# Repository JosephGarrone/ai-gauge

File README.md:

# AI-Gauge

Customisable automotive dial gauge firmware for the Waveshare
**ESP32-S3-Touch-AMOLED-1.75** (466×466 round AMOLED).

Replaces physical boost and EGT gauges, re-using the vehicle's existing sensors through an
external signal-conditioning front-end. The gauge face is defined in XML, so it can be
restyled without rebuilding firmware.

## Goals

- **60fps+**, always. A laggy needle is worse than the analogue gauge it replaces.
- **XML-defined faces** — restyle over WiFi, no rebuild, including your own tick, needle and hub
  shapes, designed in the browser with the face editor.
- **Portable** to square and other round panels via a board profile.
- **Swipe up** from the dial for settings.
- **WiFi** for config upload, OTA, and telemetry feeds pushed from other devices.

## Getting started

```bash
. ~/esp/v5.5.1/esp-idf/export.sh
idf.py -C firmware set-target esp32s3
idf.py -C firmware -p <PORT> flash monitor
```

Full instructions: [docs/build-and-flash.md](docs/build-and-flash.md).

Not developing the firmware? Every tagged release publishes a browser-based installer — flash
from Chrome or Edge with no toolchain. See [docs/ci-release.md](docs/ci-release.md).

To design a face, open the **face editor**: watch it move, check exactly what the gauge will make of
it, and download the XML. Every gauge serves it at `http://ai-gauge-XXXX.local/editor/`, and opened
from there it uploads straight to that gauge. A copy for designing without a gauge is at `/editor/`
on the GitHub Pages site. See [docs/config-app.md](docs/config-app.md).

## Documentation

Start with **[AGENTS.md](AGENTS.md)** for the design decisions and the conventions this
project follows, then [docs/](docs/) for detail:

| Document | Contents |
|---|---|
| [architecture.md](docs/architecture.md) | Components, task model, data flow |
| [display-pipeline.md](docs/display-pipeline.md) | Frame budget and how 60fps is achieved |
| [gauge-config-schema.md](docs/gauge-config-schema.md) | The gauge XML format |
| [gauge-xml-interface.md](docs/gauge-xml-interface.md) | Authoring guide for tools that write gauge XML |
| [config-app.md](docs/config-app.md) | The face editor web app |
| [hardware-reference.md](docs/hardware-reference.md) | GPIO map, I2C addresses, warnings |
| [sensor-frontend.md](docs/sensor-frontend.md) | Boost and EGT signal conditioning |
| [rear-pcb.md](docs/rear-pcb.md) | Planned rear PCB: power, daisy chain, sensors |
| [rear-pcb-parts.md](docs/rear-pcb-parts.md) | Rear PCB parts list, pinouts and wiring diagrams |
| [networking.md](docs/networking.md) | Provisioning, HTTP API, telemetry, OTA |
| [performance.md](docs/performance.md) | Measurement method and results |
| [roadmap.md](docs/roadmap.md) | Milestones and what is planned next |
| [adr/](docs/adr/) | Why things are the way they are |

## Status

Running on hardware. The sensor board has been designed and sent for fabrication, and the
firmware to read it is written, but it has not met a board yet. Until one answers, the needle
shows a **simulated** sweep.

**Working today:** the dial renders from an XML configuration held on flash, with colour
bands, ticks, labels and a damped needle. Crossing an alert threshold flashes the needle in the
alert colour. A peak-hold marker records the highest reading on the dial; tap the dial to reset
it. Long-press the dial to recall the session minimum and maximum for 3s; long-press again
while they show to reset them. Swipe up for settings — pick a different gauge, adjust brightness, rotate the screen in 90°
steps to suit how the gauge is mounted, cap the frame rate at 30, 45 or 60 fps or leave it
uncapped, toggle an FPS badge, and read live
frame statistics and firmware information. Choices persist across
reboots. The settings page also shows live sensor readings and faults, has a **Zero boost now**
button, and holds the sensor calibration (sensor range and output voltages, divider trims, EGT
offset, smoothing, auto-zero).

There is no audible alert: no speaker will be fitted, so the chime was removed.

Over WiFi, the gauge is set up from a phone and then reachable at `ai-gauge-XXXX.local`. Its HTTP
API uploads new gauge faces and applies them live, accepts telemetry from other devices, and
installs firmware updates, rolling back automatically if an update fails to start. See
[docs/networking.md](docs/networking.md); note the API is unauthenticated, so use it only on a
network you trust.

A missing or malformed configuration falls back to the next available one, and then to a
compiled-in face, always saying on the settings page what went wrong. A bad config file must
never leave a driver looking at a blank screen.

**Measured on hardware** (ESP32-S3 rev v0.2), needle sweeping continuously with WiFi connected,
peak-hold and audio running:

| | Result |
|---|---|
| Frame rate | **66.7 fps** (the LVGL refresh ceiling, not a rendering limit) |
| Screen redrawn per frame | ~13% |
| Render time | ~7.7 ms of each 15 ms period |
| Swipe transition | ~33 fps — a documented, accepted trade |
| Internal RAM free after startup | ~8.6 KB — the board's scarcest resource |

CPU is not the constraint on this board; **internal RAM is**. The display's flush buffers, WiFi's
receive buffers and every task stack all compete for the ESP32-S3's ~512 KB of internal SRAM, while
8 MB of PSRAM sits largely idle. Anything that adds a task, a stack or a small allocation has to
be measured. The rules are in [AGENTS.md](AGENTS.md).

Method, the renderer designs that failed, and how each memory limit was found and fixed, are in
[docs/performance.md](docs/performance.md).

## Roadmap

Detail and exit criteria in [docs/roadmap.md](docs/roadmap.md).

| | Milestone | State |
|---|---|---|
| M1 | Foundation: docs, build, XML parser, CI, display bring-up | ✅ |
| M2 | Renderer and screens; the 60fps gate | ✅ |
| M3 | Load configurations from flash; switch gauges at runtime | ✅ |
| M4 | WiFi: provisioning, config upload, telemetry feeds, OTA | ✅ |
| **M5** | **Sensors: boost via ADS1115, EGT via ADS1115 + TMP1075 cold junction** | **🚧 firmware done; board at fab** |
| **M6** | **Alerts, peak-hold, min/max recall, datalogging** | **🚧 in progress** |
| **M7** | **Web app for designing gauge faces** | **🚧 in progress** |
| M8 | Portability: square and other round panels | |

M6 so far: needle alert flash and peak-hold are verified on hardware; the chime was dropped (no
speaker). SD datalogging waits for a card.

M7 so far: the gauge serves the face editor, and faces upload from it, verified on hardware. The
GitHub Pages copy awaits its first deploy, and the frame cost of a custom-shaped needle is still to
be measured.

Software comes before sensors deliberately. The sensor board still has to be built, and the
firmware treats a simulated source, a network feed and a real sensor identically — so the
whole UI and network stack can be finished and verified before any wiring exists.

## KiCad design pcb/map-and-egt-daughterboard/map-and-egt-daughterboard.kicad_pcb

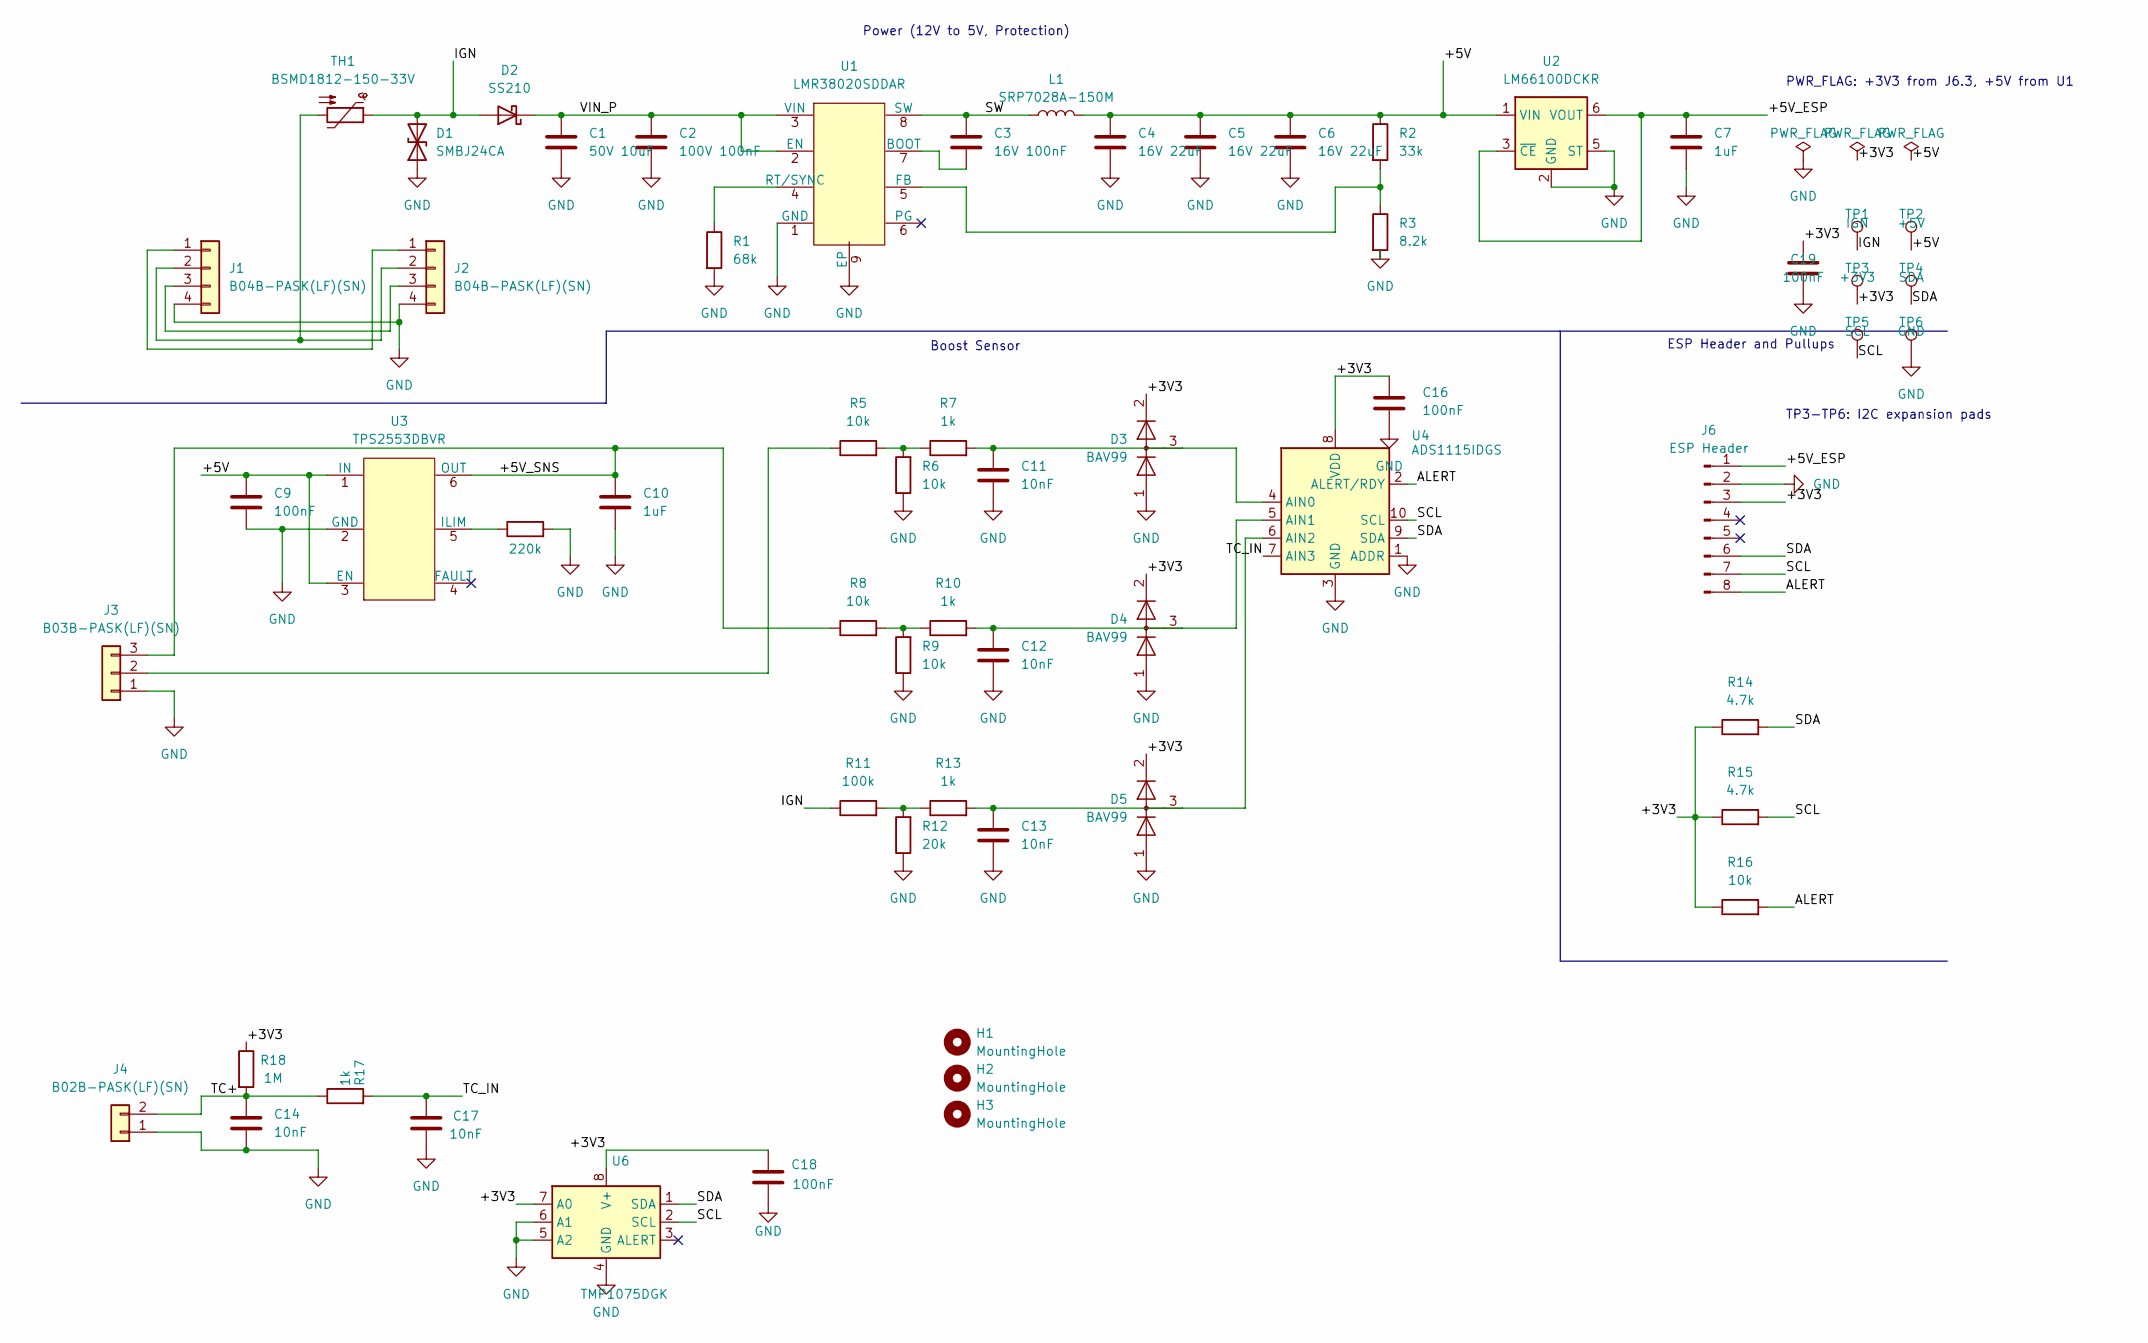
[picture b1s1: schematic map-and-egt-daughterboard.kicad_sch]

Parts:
C1: 50V 10uF; C_0805_2012Metric; LCSC C440198
C2: 100V 100nF; C_0805_2012Metric; LCSC C28233
C3: 16V 100nF; C_0805_2012Metric; LCSC C49678
C4, C5, C6: 16V 22uF; C_0805_2012Metric; LCSC C45783
C7, C10: 1uF; C_0805_2012Metric; LCSC C28323
C9, C16, C18: 100nF; C_0805_2012Metric; LCSC C49678
C11, C12, C13: 10nF; C_0603_1608Metric; LCSC C57112
C14, C17: 10nF; C_0805_2012Metric; LCSC C1710
C19: 100nF; C_0603_1608Metric; LCSC C14663
D1: SMBJ24CA; D_SMB; LCSC C78416
D2: SS210; D_SMA; LCSC C14996
D3, D4, D5: BAV99; SOT-23; LCSC C2500
H1, H2, H3: MountingHole; MountingHole_2.2mm_M2
J1, J2: B04B-PASK(LF)(SN); JST_PH_B4B-PH-K_1x04_P2.00mm_Vertical
J3: B03B-PASK(LF)(SN); JST_PH_B3B-PH-K_1x03_P2.00mm_Vertical
J4: B02B-PASK(LF)(SN); JST_PH_B2B-PH-K_1x02_P2.00mm_Vertical
J6: ESP Header; PinHeader_1x08_P2.54mm_Vertical
L1: SRP7028A-150M; L_Bourns_SRP7028A_7.3x6.6mm; LCSC C1847948
R1: 68k; R_0805_2012Metric; LCSC C17801
R2: 33k; R_0805_2012Metric; LCSC C17633
R3: 8.2k; R_0805_2012Metric; LCSC C17828
R4: 220k; R_0805_2012Metric; LCSC C17556
R5, R6, R8, R9, R16: 10k; R_0805_2012Metric; LCSC C17414
R7, R10, R13, R17: 1k; R_0805_2012Metric; LCSC C17513
R11: 100k; R_0805_2012Metric; LCSC C149504
R12: 20k; R_0805_2012Metric; LCSC C4328
R14, R15: 4.7k; R_0805_2012Metric; LCSC C17673
R18: 1M; R_0805_2012Metric; LCSC C17514
TH1: BSMD1812-150-33V; R_1812_4532Metric; LCSC C883154
TP1: IGN; TestPoint_Pad_D1.5mm
TP2: +5V; TestPoint_Pad_D1.5mm
TP3: +3V3; TestPoint_Pad_D1.5mm
TP4: SDA; TestPoint_Pad_D1.5mm
TP5: SCL; TestPoint_Pad_D1.5mm
TP6: GND; TestPoint_Pad_D1.5mm
U1: LMR38020SDDAR; Texas_HSOP-8-1EP_3.9x4.9mm_P1.27mm; LCSC C3192337
U2: LM66100DCKR; SOT-363_SC-70-6; LCSC C2869734
U3: TPS2553DBVR; SOT-23-6; LCSC C55266
U4: ADS1115IDGS; TSSOP-10_3x3mm_P0.5mm; LCSC C37593
U6: TMP1075DGK; VSSOP-8_3x3mm_P0.65mm; LCSC C2864807

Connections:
/+3V3: C16.1, C18.1, C19.1, D3.2 (A), D4.2 (A), D5.2 (A), J6.3, R14.1, R15.1, R16.1, R18.1, TP3.1, U4.8 (VDD), U6.7 (A0), U6.8 (V+)
/+5V: C4.1, C5.1, C6.1, C9.1, L1.2, R2.1, TP2.1, U2.1 (VIN), U3.1 (IN), U3.3 (EN)
/+5V_ESP: C7.1, J6.1, U2.3 (~CE), U2.6 (VOUT)
/+5V_SNS: C10.1, J3.3, R8.1, U3.6 (OUT)
/ALERT: J6.8, R16.2, U4.2 (ALERT/RDY)
/IGN: D1.2 (A2), D2.2 (A), R11.1, TH1.1, TP1.1
/SCL: J6.7, R15.2, TP5.1, U4.10 (SCL), U6.2 (SCL)
/SDA: J6.6, R14.2, TP4.1, U4.9 (SDA), U6.1 (SDA)
/SW: C3.1, L1.1, U1.8 (SW)
/TC+: C14.1, J4.2, R17.1, R18.2
/TC_IN: C17.1, R17.2, U4.7 (AIN3)
/VIN_P: C1.1, C2.1, D2.1 (K), U1.2 (EN), U1.3 (VIN)
GND: C1.2, C2.2, C4.2, C5.2, C6.2, C7.2, C9.2, C10.2, C11.2, C12.2, C13.2, C14.2, C16.2, C17.2, C18.2, C19.2, D1.1 (A1), D3.1 (K), D4.1 (K), D5.1 (K), J1.4, J2.4, J3.1, J4.1, J6.2, R1.2, R3.2, R4.2, R6.1, R9.1, R12.1, TP6.1, U1.1 (GND), U1.9 (EP), U2.2 (GND), U2.5 (ST), U3.2 (GND), U4.1 (ADDR), U4.3 (GND), U6.4 (GND), U6.5 (A2), U6.6 (A1)
unnamed: J1.1, J2.1
unnamed: J1.2, J2.2, TH1.2
unnamed: J1.3, J2.3
unnamed: J3.2, R5.1
unnamed: R5.2, R6.2, R7.1
unnamed: R8.2, R9.2, R10.1
unnamed: R11.2, R12.2, R13.1
unnamed: C3.2, U1.7 (BOOT)
unnamed: R2.2, R3.1, U1.5 (FB)
unnamed: R1.1, U1.4 (RT/SYNC)
unnamed: R4.1, U3.5 (ILIM)
unnamed: C11.1, D3.3 (K), R7.2, U4.4 (AIN0)
unnamed: C12.1, D4.3 (K), R10.2, U4.5 (AIN1)
unnamed: C13.1, D5.3 (K), R13.2, U4.6 (AIN2)

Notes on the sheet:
Power (12V to 5V, Protection)
ESP Header and Pullups
Boost Sensor
PWR_FLAG: +3V3 from J6.3, +5V from U1
TP3-TP6: I2C expansion pads

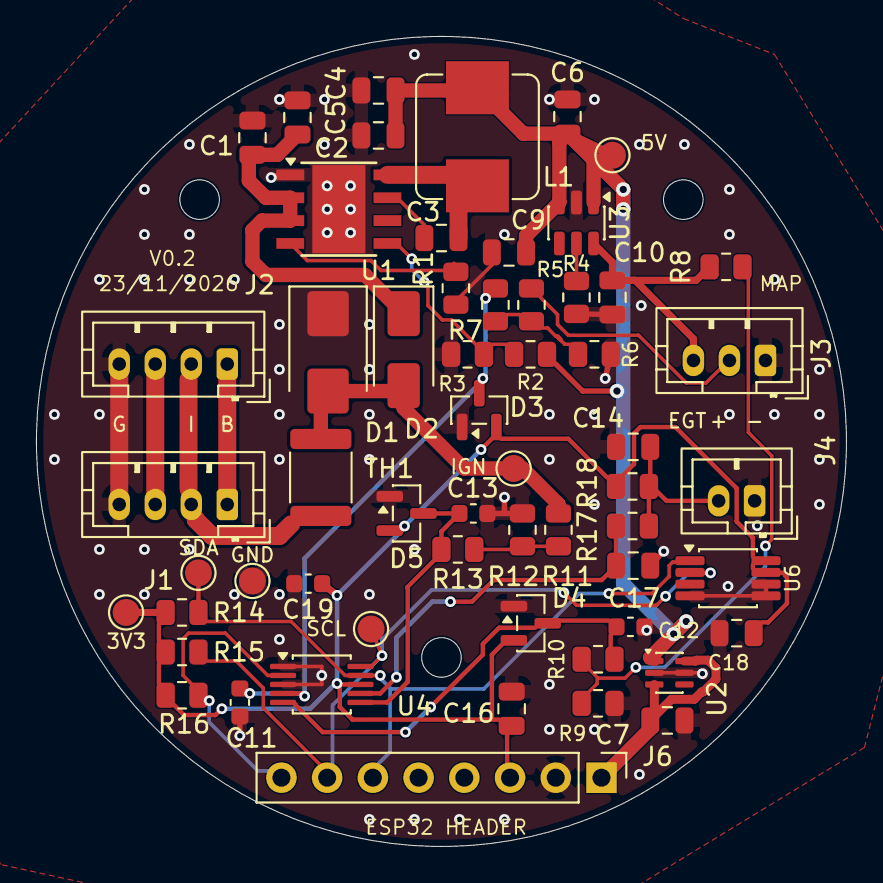
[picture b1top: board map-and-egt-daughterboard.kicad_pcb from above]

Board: 2 copper layers, 45.0 x 45.0 mm, 61 parts (0 on the bottom side), 27 nets.
